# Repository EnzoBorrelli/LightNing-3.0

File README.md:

# LightNing 3.0

This is the 3rd version of my esp32 + Dualshock4® Rc car, it has the pc made entirely out of smd pieces

## Installation

Download the files. Install KiCad for the PCB and any arduino code editor of your preference (I use Arduino IDE)

## Usage
In the IDE, you must install the ESP32 board and the bluepad 32 library:
[How to install](https://github.com/ricardoquesada/bluepad32#how-to-compile-it)
[original repo](https://github.com/ricardoquesada/bluepad32#bluepad32)

## Contributing

Pull requests are welcome. For major changes, please open an issue first
to discuss what you would like to change.

Please make sure to update tests as appropriate.

## License

[MIT](https://choosealicense.com/licenses/mit/)

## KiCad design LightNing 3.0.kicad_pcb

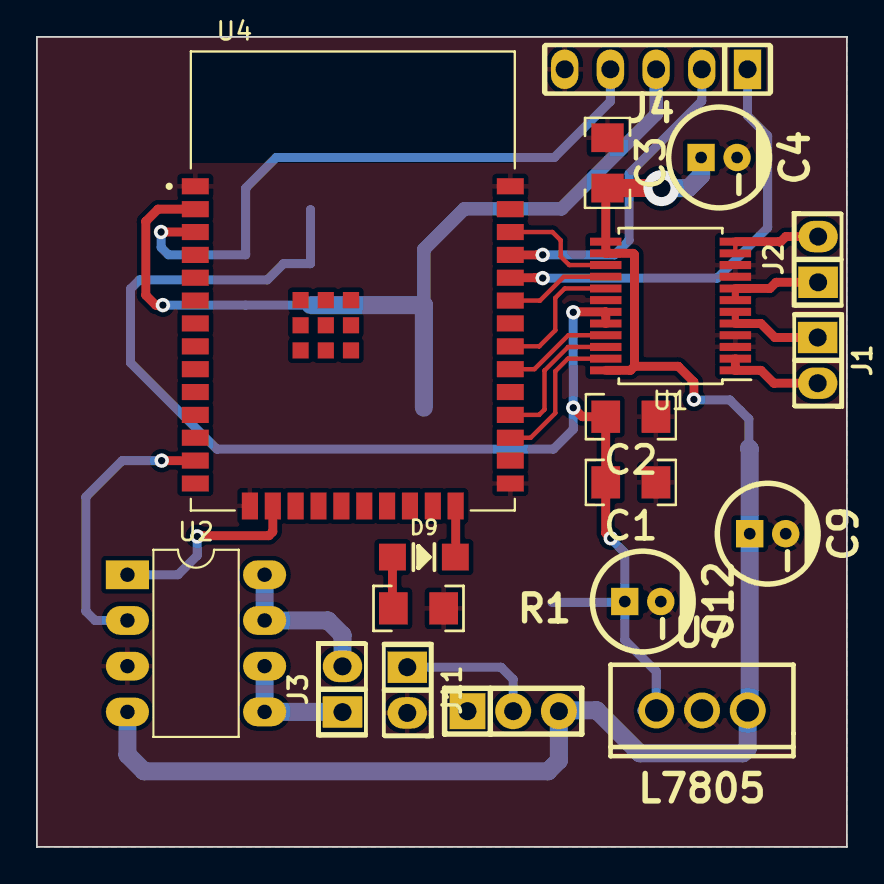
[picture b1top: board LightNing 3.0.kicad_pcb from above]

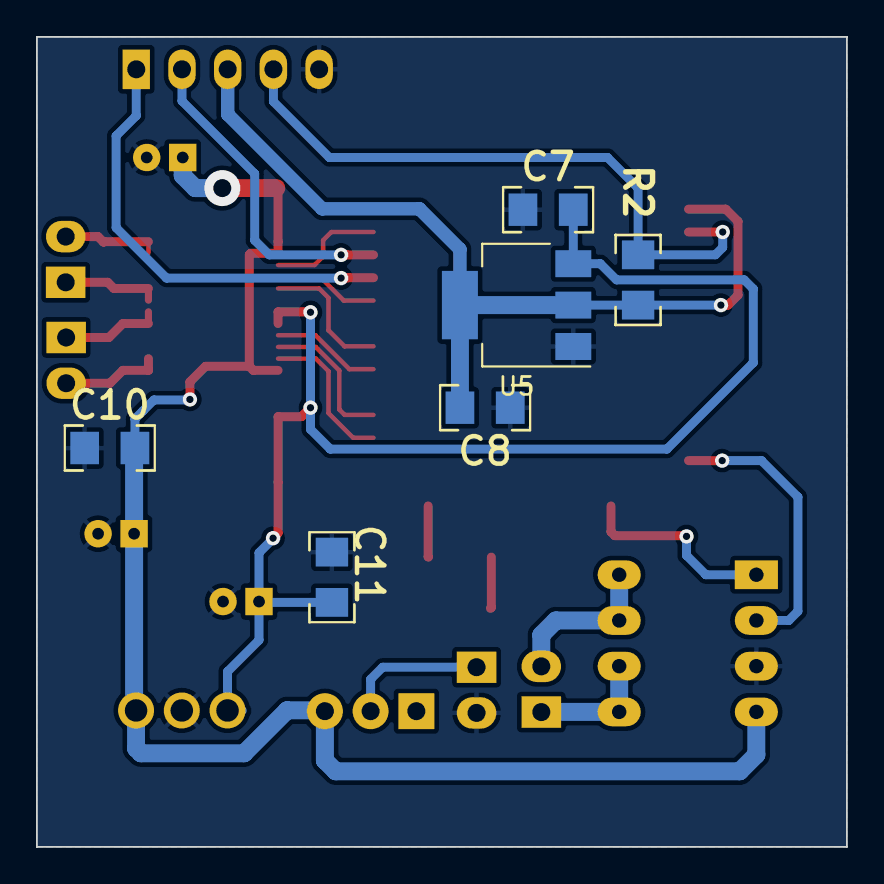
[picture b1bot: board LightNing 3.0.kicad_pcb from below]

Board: 2 copper layers, 45.0 x 45.0 mm, 24 parts (6 on the bottom side), 24 nets.

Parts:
C1, C3, C7: 10uF; C_1206
C2, C10, C11: 100nF; C_1206
C4: 22uF 25v; CAP_ELEC_5x11mm
C8: 22uF; C_1206
C9: 100uF 25v; CAP_ELEC_5x11mm
C12: 10uF 16v; CAP_ELEC_5x11mm
D9: LED; LED_1206
J1: motor izq; Pin_Header_2
J2: motor der; Pin_Header_2
J3: motor dir; Pin_Header_2
J4: programmer; Pin_Strip_5
J11: batt; Pin_Header_2
R1: 220; R_1206
R2: 10k; R_1206
SW2: SW_SPDT; Pin_Strip_3
U1: TB6612FNG; SSOP-24_5.3x8.2mm_P0.65mm
U2: TA6586; DIP-8
U4: ESP32-WROOM-E; XCVR_ESP32-WROOM-32E__16MB_
U5: AMS1117-3.3; SOT-223-3_TabPin2
U7: L7805; TO-220

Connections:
+3.3V: C8.1, J4.3, R2.1, U4.2 (3V3), U5.2 (VO)
+5V: C1.1, C2.1, C7.1, C11.1, C12.1, U1.19 (STBY), U1.20 (VCC), U5.3 (VI), U7.3 (OUT)
/IN1: U1.21 (AIN1), U4.30 (GPIO18)
/IN2: U1.22 (AIN2), U4.28 (GPIO17)
/IN3: U1.17 (BIN1), U4.31 (GPIO19)
/IN4: U1.16 (BIN2), U4.33 (GPIO21)
/PWA: U1.23 (PWMA), U4.27 (GPIO16)
/PWB: U1.15 (PWMB), U4.36 (GPIO22)
/en: J4.4, R2.2, U4.3 (EN/CHIP_PU)
/pin_dirA: U2.2 (FI), U4.13 (MTMS/GPIO14/ADC2_CH6)
/pin_dirB: U2.1 (BI), U4.16 (MTCK/GPIO13/ADC2_CH4)
/rx: J4.1, U4.34 (U0RXD/GPIO3)
/tx: J4.2, U4.35 (U0TXD/GPIO1)
GND: C1.2, C2.2, C3.2, C4.2, C7.2, C8.2, C9.2, C10.2, C11.2, C12.2, J4.5, J11.2, R1.2, U1.3 (PGND1), U1.4 (PGND1), U1.9 (PGND2), U1.10 (PGND2), U1.18 (GND), U2.3 (GND), U4.1 (GND), U4.15 (GND), U4.25 (GPIO0/BOOT/ADC2_CH1), U4.38 (GND), U5.1 (GND), U7.2 (GND)
unnamed: D9.2 (A), U4.24 (ADC2_CH2/GPIO2)
unnamed: D9.1 (K), R1.1
unnamed: J1.1, U1.5 (AO2), U1.6 (AO2)
unnamed: J1.2, U1.1 (AO1), U1.2 (AO1)
unnamed: J2.1, U1.7 (BO2), U1.8 (BO2)
unnamed: J2.2, U1.11 (BO1), U1.12 (BO1)
unnamed: J3.1, U2.5 (FO), U2.6 (FO)
unnamed: J3.2, U2.7 (BO), U2.8 (BO)
unnamed: J11.1, SW2.2 (B)
VCC: C3.1, C4.1, C9.1, C10.1, SW2.3 (C), U1.13 (VM2), U1.14 (VM3), U1.24 (VM1), U2.4 (VCC), U7.1 (IN)

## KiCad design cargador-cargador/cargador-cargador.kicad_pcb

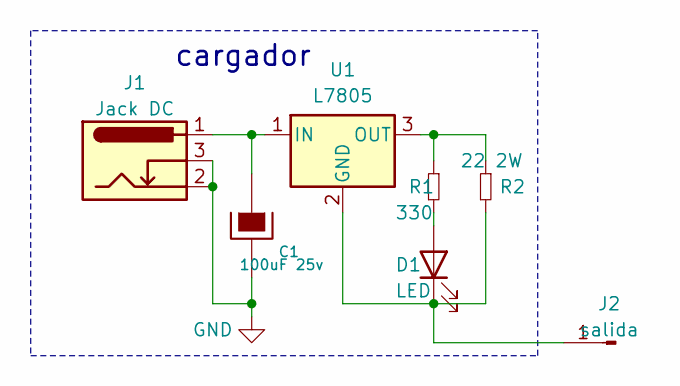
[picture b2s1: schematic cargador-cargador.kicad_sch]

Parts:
C1: 100uF 25v; CAP_ELEC_5x11mm
D1: LED; Pin_strip_2
J1: Jack DC; BarrelJack_Kycon_KLDX-0202-xC_Horizontal
J2: salida; hole_1mm
R1: 330; RES0.3
R2: 22 2W; RES0.3
U1: L7805; TO-220

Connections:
GND: C1.2, J1.2, J1.3
unnamed: D1.2 (A), R1.2
unnamed: D1.1 (K), J2.1, R2.2, U1.2 (GND)
unnamed: C1.1, J1.1, U1.1 (IN)
unnamed: R1.1, R2.1, U1.3 (OUT)

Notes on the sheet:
cargador

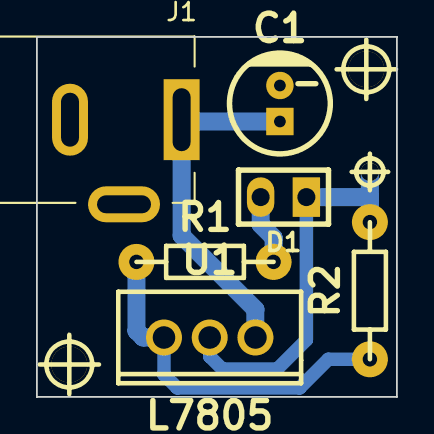
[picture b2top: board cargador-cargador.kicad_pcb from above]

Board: 2 copper layers, 20.0 x 20.0 mm, 9 parts (0 on the bottom side), 5 nets.

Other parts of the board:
hole_2mm, hole_2mm#2: VAL**; hole_2mm

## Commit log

2023-05-15 uno cambio lokos
2023-05-18 agregado el cargador
2023-05-19 little responsive
2023-09-28 rework
2023-10-30 pcb terminado
2023-11-01 update 1 november
